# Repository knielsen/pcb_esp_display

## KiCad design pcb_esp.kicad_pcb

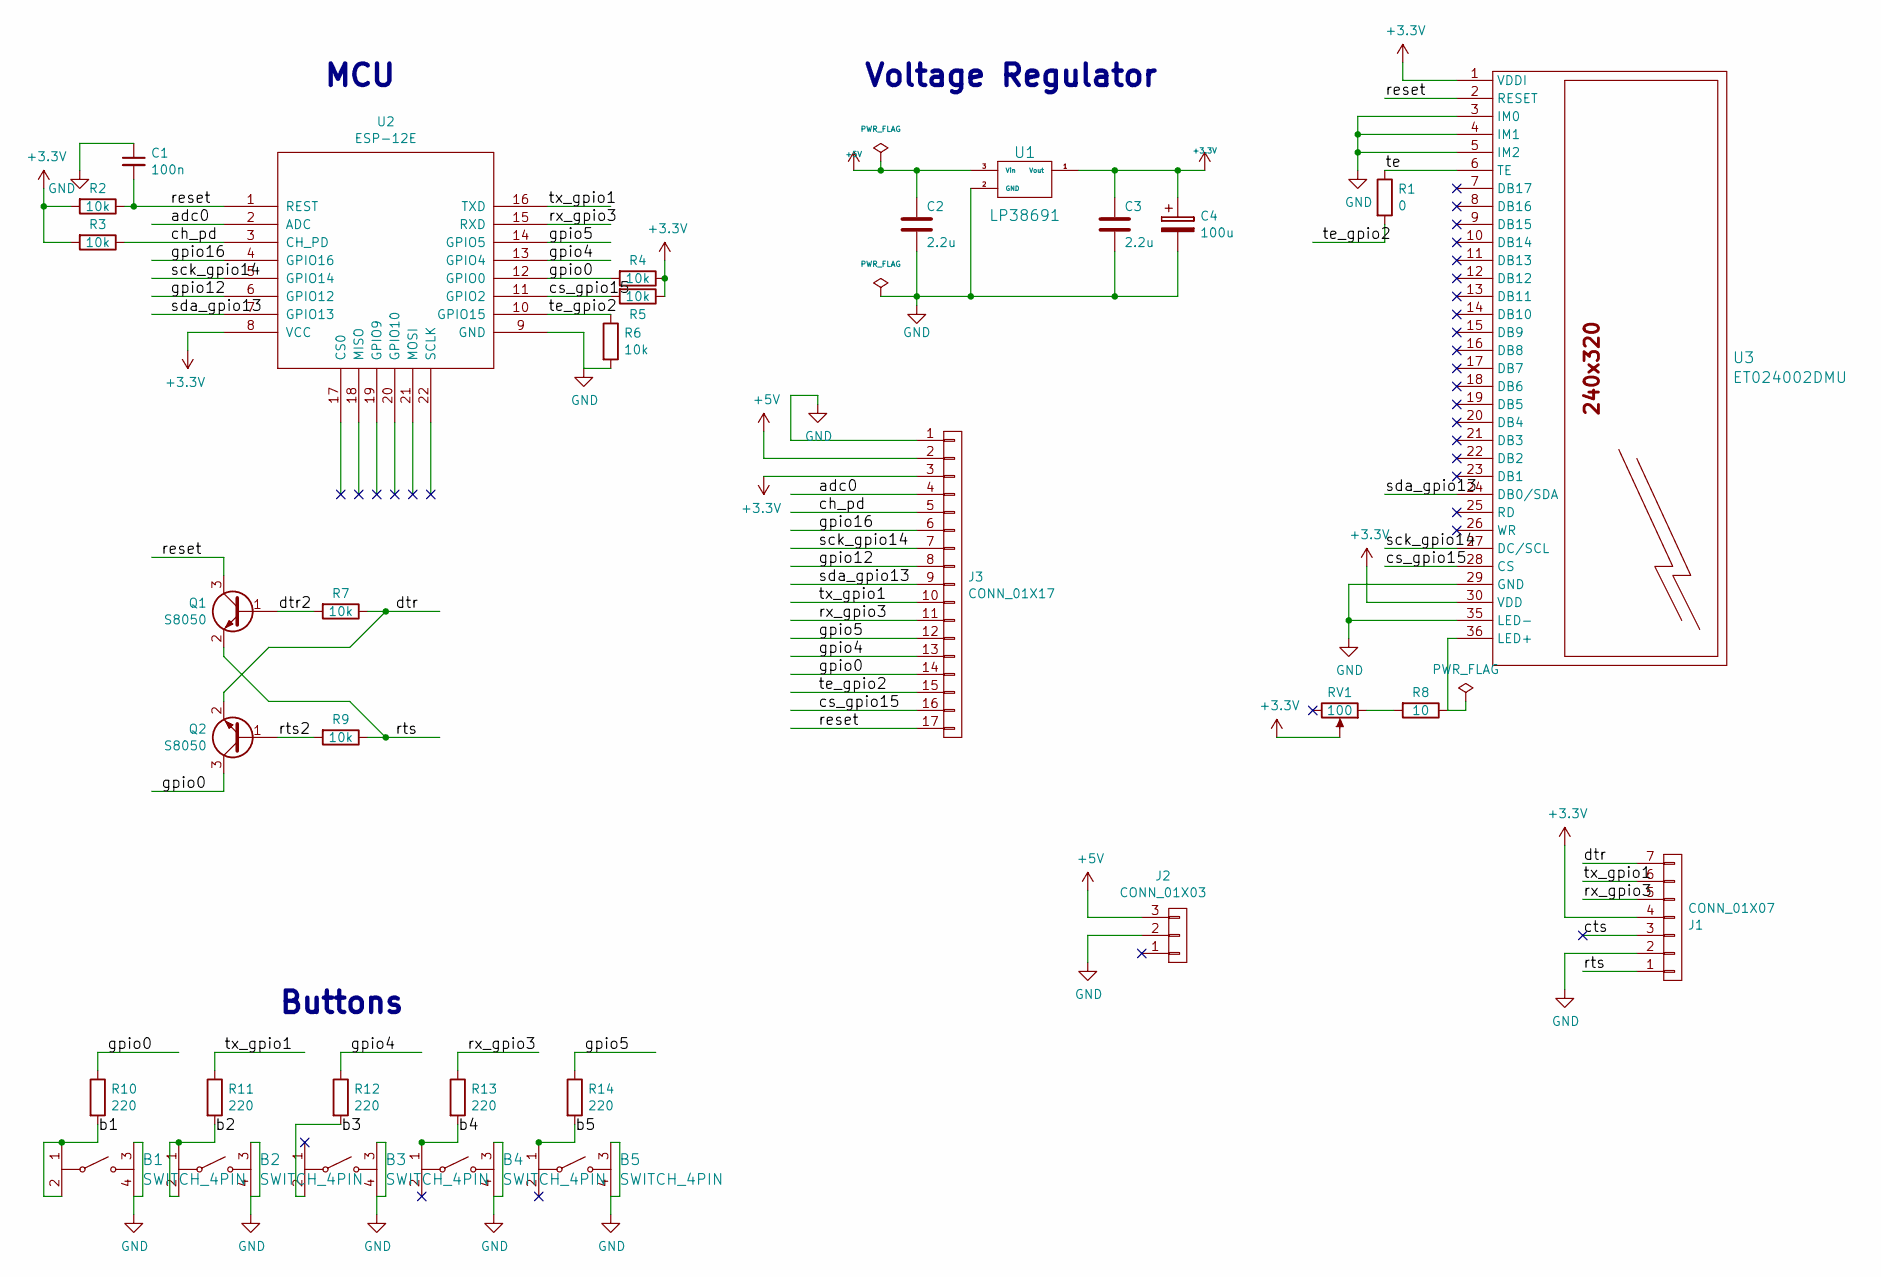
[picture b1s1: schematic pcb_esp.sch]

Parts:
B1, B2, B3, B4, B5: SWITCH_4PIN; SW_TH_Tactile_Omron_B3F-10xx
C1: 100n; C_0805_HandSoldering
C2, C3: 2.2u; C_0805_HandSoldering
C4: 100u; CP_Tantalum_Case-U_EIA-6032-15_Hand
J1: CONN_01X07; Pin_Header_Angled_1x07_Pitch2.54mm
J2: CONN_01X03; con-jack-DCJ0303
J3: CONN_01X17; Pin_Header_Angled_1x17_Pitch2.54mm
Q1, Q2: S8050; SOT-23_Handsoldering
R1: 0; R_1206_HandSoldering
R2, R3, R4, R5, R6, R7, R9: 10k; R_0805_HandSoldering
R8: 10; R_0805_HandSoldering
R10, R11, R12, R13, R14: 220; R_1206_HandSoldering
RV1: 100; Potentiometer_Trimmer_Bourns_3296W
U1: LP38691; TO-252-3
U2: ESP-12E; ESP-12E_SMD
U3: ET024002DMU; ET024002DMU_otherside

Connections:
+3V3: C3.1, C4.1, J1.4, J3.3, R2.2, R3.2, R4.1, R5.1, RV1.2, U1.1 (Vout), U2.8 (VCC), U3.1 (VDDI), U3.30 (VDD)
+5V: C2.1, J2.3, J3.2, U1.3 (Vin)
/adc0: J3.4, U2.2 (ADC)
/b1: B1.1, B1.2, R10.2
/b2: B2.1, B2.2, R11.2
/b4: B4.1, R13.2
/b5: B5.1, R14.2
/ch_pd: J3.5, R3.1, U2.3 (CH_PD)
/cs_gpio15: J3.16, R5.2, U2.11 (GPIO2), U3.28 (CS)
/cts: J1.3
/dtr: J1.7, Q2.2 (E), R7.1
/dtr2: Q1.1 (B), R7.2
/gpio0: J3.14, Q2.3 (C), R4.2, R10.1, U2.12 (GPIO0)
/gpio4: J3.13, R12.1, U2.13 (GPIO4)
/gpio5: J3.12, R14.1, U2.14 (GPIO5)
/gpio12: J3.8, U2.6 (GPIO12)
/gpio16: J3.6, U2.4 (GPIO16)
/reset: C1.2, J3.17, Q1.3 (C), R2.1, U2.1 (REST), U3.2 (RESET)
/rts: J1.1, Q1.2 (E), R9.1
/rts2: Q2.1 (B), R9.2
/rx_gpio3: J1.5, J3.11, R13.1, U2.15 (RXD)
/sck_gpio14: J3.7, U2.5 (GPIO14), U3.27 (DC/SCL)
/sda_gpio13: J3.9, U2.7 (GPIO13), U3.24 (DB0/SDA)
/te: R1.1, U3.6 (TE)
/te_gpio2: J3.15, R1.2, R6.1, U2.10 (GPIO15)
/tx_gpio1: J1.6, J3.10, R11.1, U2.16 (TXD)
GND: B1.3, B1.4, B2.3, B2.4, B3.3, B3.4, B4.3, B4.4, B5.3, B5.4, C1.1, C2.2, C3.2, C4.2, J1.2, J2.2, J3.1, R6.2, U1.2 (GND), U2.9 (GND), U3.3 (IM0), U3.4 (IM1), U3.5 (IM2), U3.29 (GND), U3.35 (LED-)
unnamed: B3.2, R12.2
unnamed: R8.1, U3.36 (LED+)
unnamed: R8.2, RV1.1

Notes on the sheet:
Voltage Regulator
MCU
Buttons

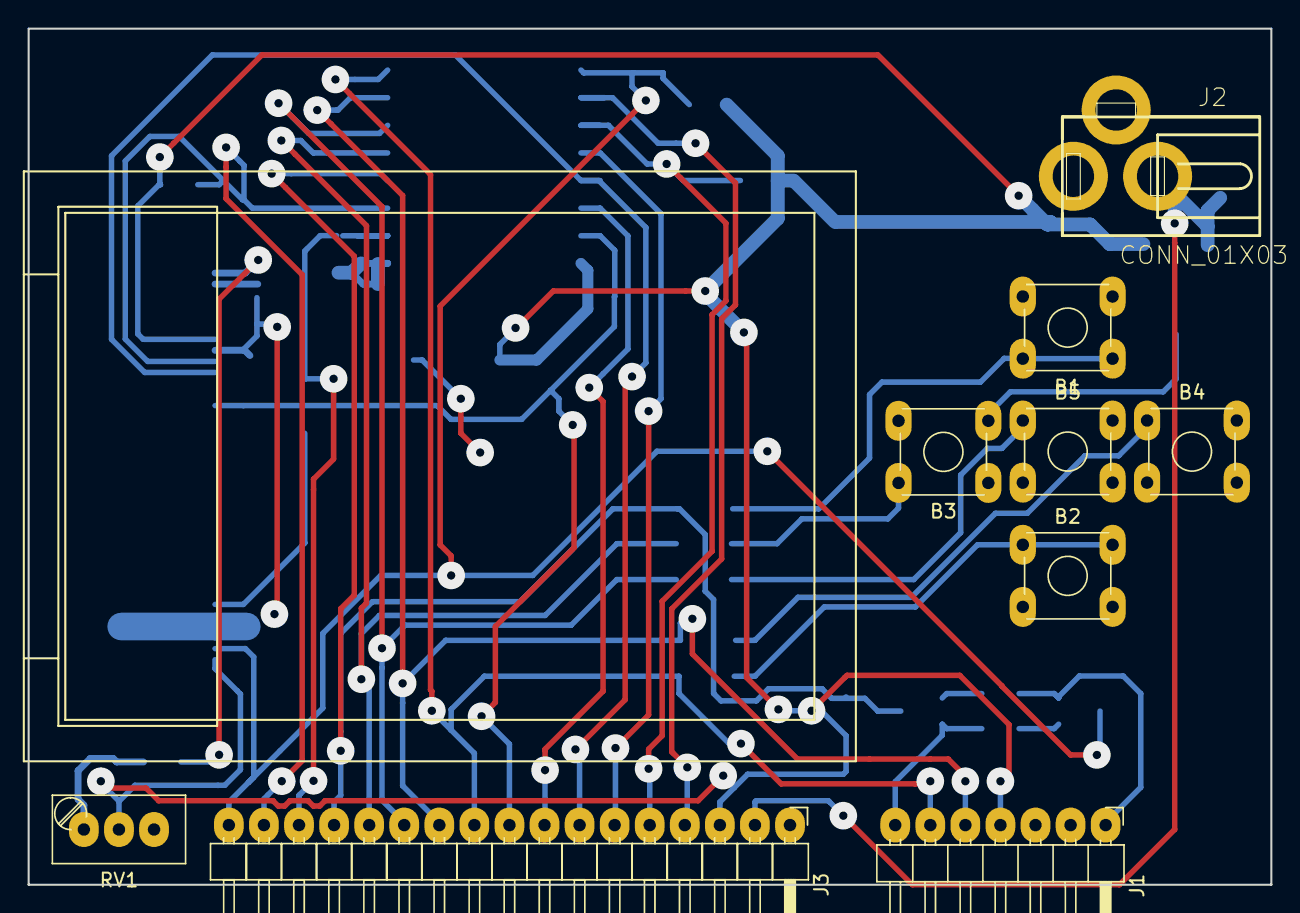
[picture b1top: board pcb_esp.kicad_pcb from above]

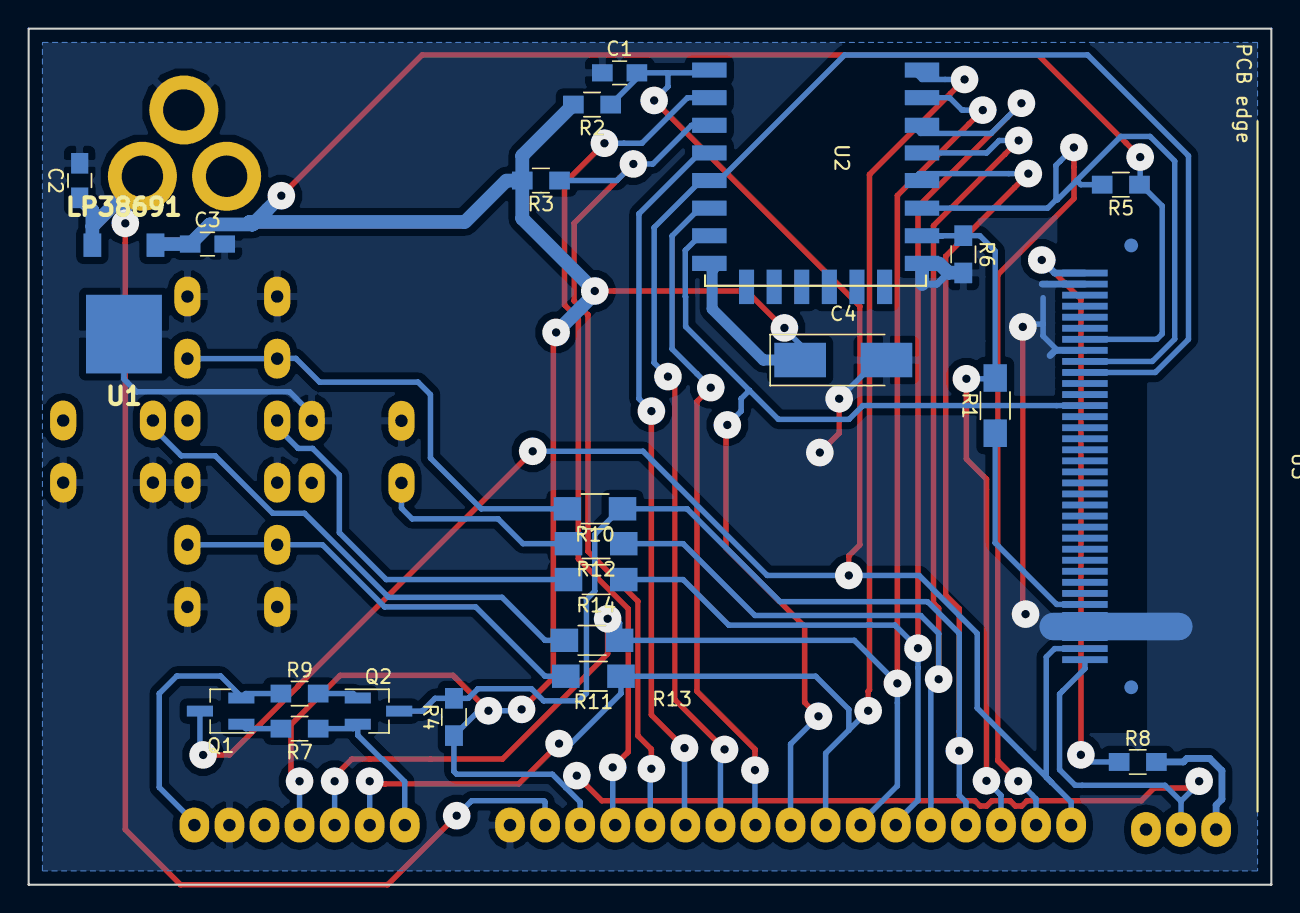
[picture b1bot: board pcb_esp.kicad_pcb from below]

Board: 2 copper layers, 90.0 x 62.0 mm, 32 parts (23 on the bottom side), 29 nets.

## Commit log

2017-07-19 Initial version
2017-07-20 smd transistors + minor changes
    transistors changed to smd
    programming header changed to angled
    minor routing and 3d model alignment changes
2017-07-21 routing
    minor routing changes, moved a few vias, changed trace thickness a few places
2017-07-21 Tweak vias a bit for easier soldering
